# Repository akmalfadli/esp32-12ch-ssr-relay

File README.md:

# ESP32 + W5500 WebServer

## Overview
The Wemos32 12-Channel SSR Relay Controller is a smart switching system based on the ESP32 development board. It utilizes Solid State Relays (SSR) for controlling AC loads and features an Ethernet module (W5500) for network communication. The design is optimized for industrial and home automation applications, offering secure, remote-controlled relay switching.

## Features
Features

- ESP32-based control with Wi-Fi and Ethernet connectivity.
- 12-channel SSR relay control using G3MB-202P relays.
- W5500 Ethernet module for reliable wired communication.
- OLED 0.96-inch display for status monitoring.
- Secure API for remote control using authentication.
- Power supply management with AMS1117 3.3V regulator.
- Fuse protection for safety.

## Hardware Components
### 1. **Microcontroller**
- **ESP32-DEVKITC-32D** (provides Wi-Fi and Ethernet control)
- **Connected to W5500 Ethernet module** via SPI

### 2. **Relay Switching System**
- **12x G3MB-202P SSR relays** for AC load switching
- **Transistor drivers (SS8050)** for relay activation
- **LED indicators** for relay status

### 3. **Power Supply**
- **5V to 3.3V AMS1117 voltage regulator**
- **Multiple fuses for overcurrent protection**
- **External power input via barrel jack**

## Wiring Diagram
| Component | ESP32 Pin |
|-----------|----------|
| W5500 SPI MISO | GPIO 19 |
| W5500 SPI MOSI | GPIO 23 |
| W5500 SPI SCK  | GPIO 18 |
| W5500 SPI CS   | GPIO 5  |
| W5500 INT      | GPIO 4  |
| OLED SDA       | GPIO 21 |
| OLED SCL       | GPIO 22 |
| Relay 1-12     | GPIO 2, 16, 17, 13, 15, 14, 12, 25, 26, 33, 32, 27 |

## Installation & Setup
1. **Install Arduino IDE** (if not installed already).
2. **Install ESP32 Board Package**:
   - Open Arduino IDE.
   - Go to `File` > `Preferences`.
   - Add `https://dl.espressif.com/dl/package_esp32_index.json` to "Additional Board Manager URLs".
   - Go to `Tools` > `Board` > `Boards Manager`.
   - Search for `ESP32` and install the latest version.
3. **Install Required Libraries**
4. **Upload Code**:
   - Open the Arduino sketch.
   - Select your board (`ESP32 Wrover Module`).
   - Connect the ESP32 and upload the code.
   - Github repo for Arduino code [a link](https://github.com/akmalfadli/esp32-12ch-eth)

## Static IP Configuration
Modify the `setup()` function in your Arduino sketch:
```cpp
Ethernet.begin(mac, ip, myDns, gateway, subnet);
```
Example static IP settings:
```cpp
IPAddress ip(192, 168, 11, 51);
IPAddress gateway(192, 168, 11, 1);
IPAddress subnet(255, 255, 255, 0);
IPAddress myDns(8, 8, 8, 8);
```

## API Endpoints
| Method | Endpoint        | Description          |
|--------|----------------|----------------------|
| GET    | `/relay-state?ch=`      | Get device status   |
| POST   | `/relay?ch=2&state=0`    | Turn relay ON and OFF      |
| POST   | `set-auth?new-key`   |Set bearer token key     |

## Troubleshooting
### Compilation Errors
- **Ensure ESP32 is selected** in `Tools` > `Board`.
- **Check for duplicate libraries** in `Arduino/libraries/` and remove conflicting versions.
- **Reduce SPI clock speed** if Ethernet is unstable:
  ```cpp
  #define ETH_SPI_CLOCK 8000000  // Set to 8MHz
  ```

## Troubleshooting
- **No Ethernet Connection** → Check **W5500 wiring** and **IP settings**.
- **Relays not Switching** → Ensure **power supply** and **correct GPIO connections**.
- **OLED Display not Working** → Confirm **I2C address (default: 0x3C)**.

## Future Enhancements
- **Add MQTT for IoT integration**.
- **Web-based control panel** for easier relay management.
- **RTC for scheduled relay operations**.

## License
This project is open-source and licensed under the MIT License.

---
Made with ❤️ by Akmal Fadli - Perwira Teknologi Informasi

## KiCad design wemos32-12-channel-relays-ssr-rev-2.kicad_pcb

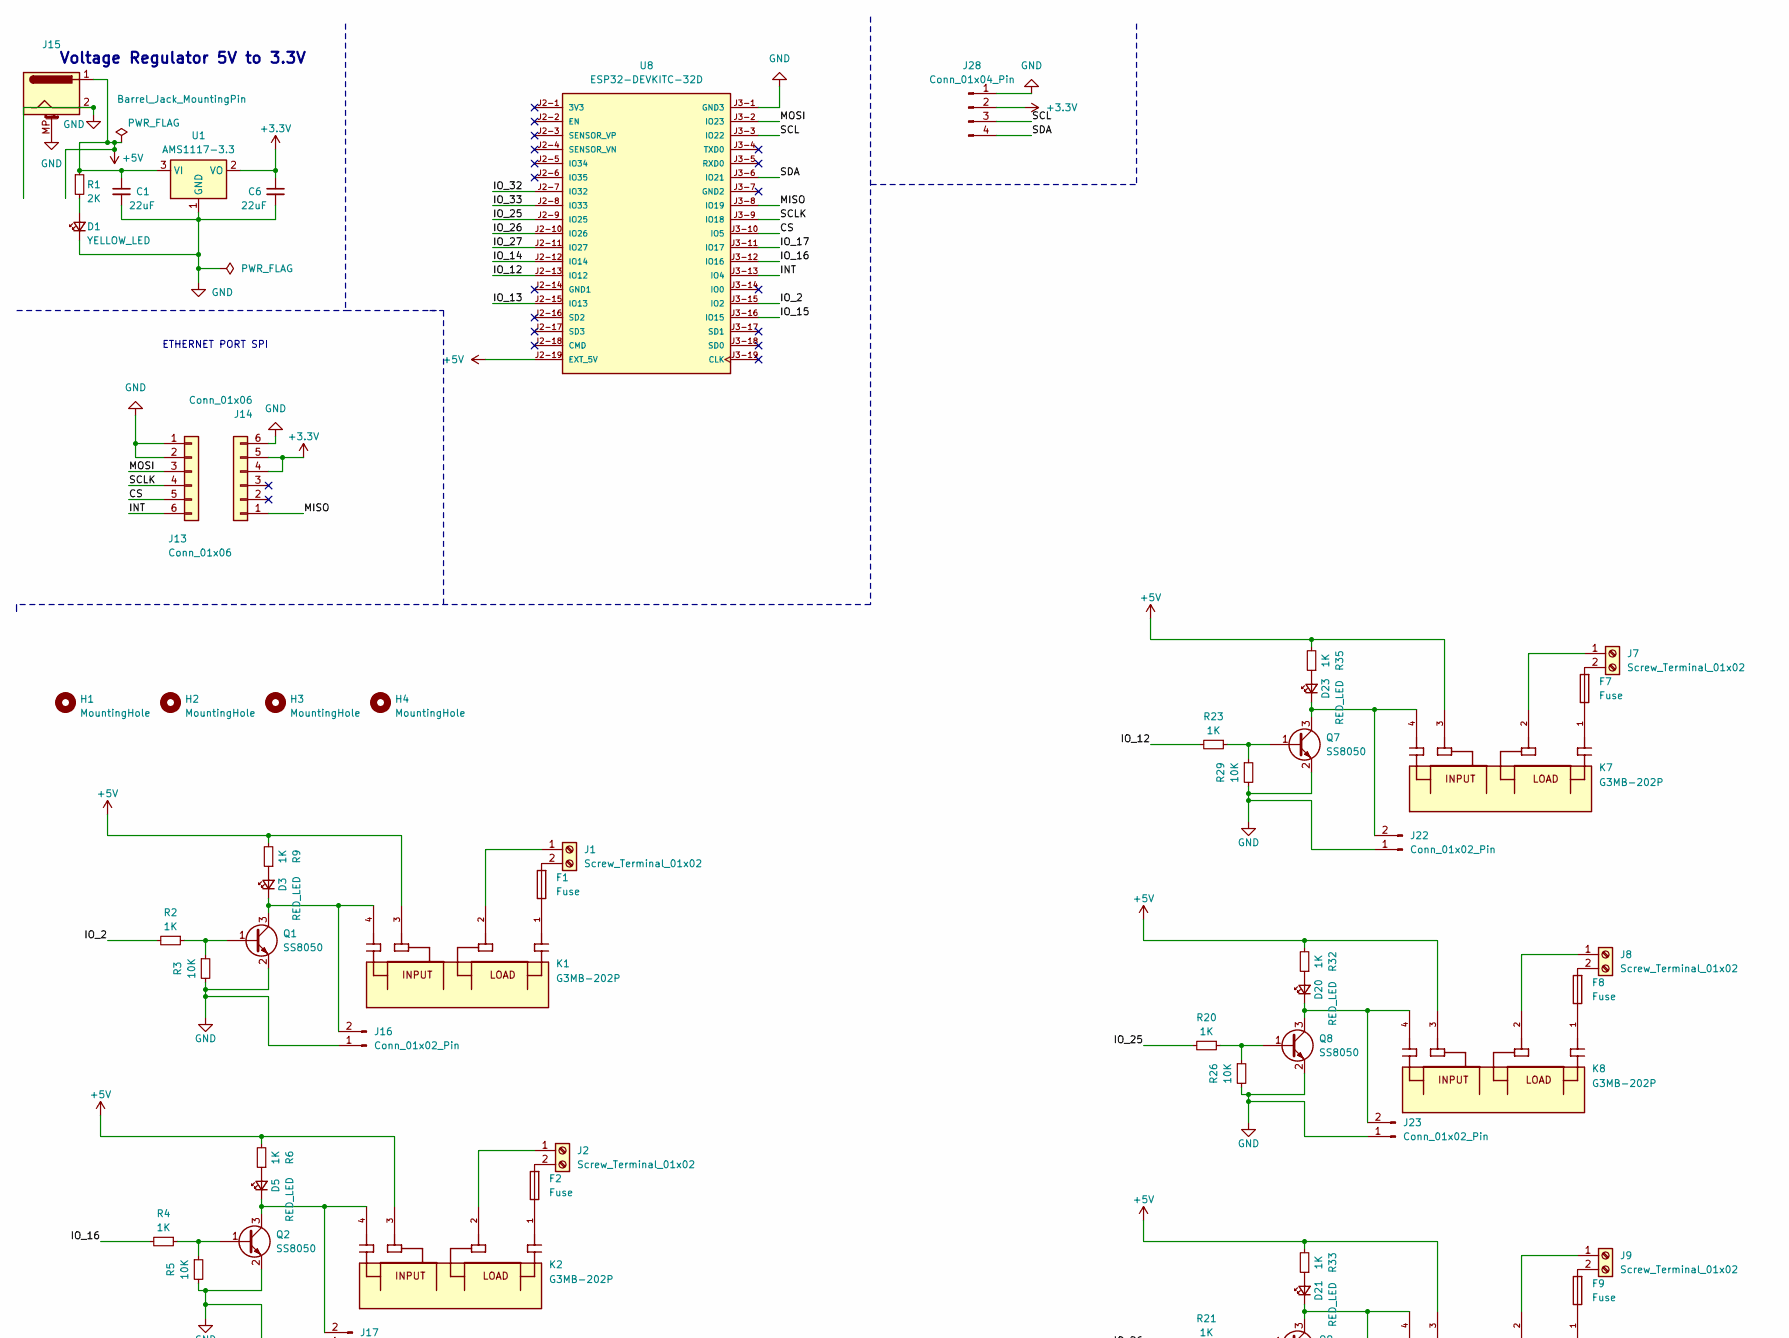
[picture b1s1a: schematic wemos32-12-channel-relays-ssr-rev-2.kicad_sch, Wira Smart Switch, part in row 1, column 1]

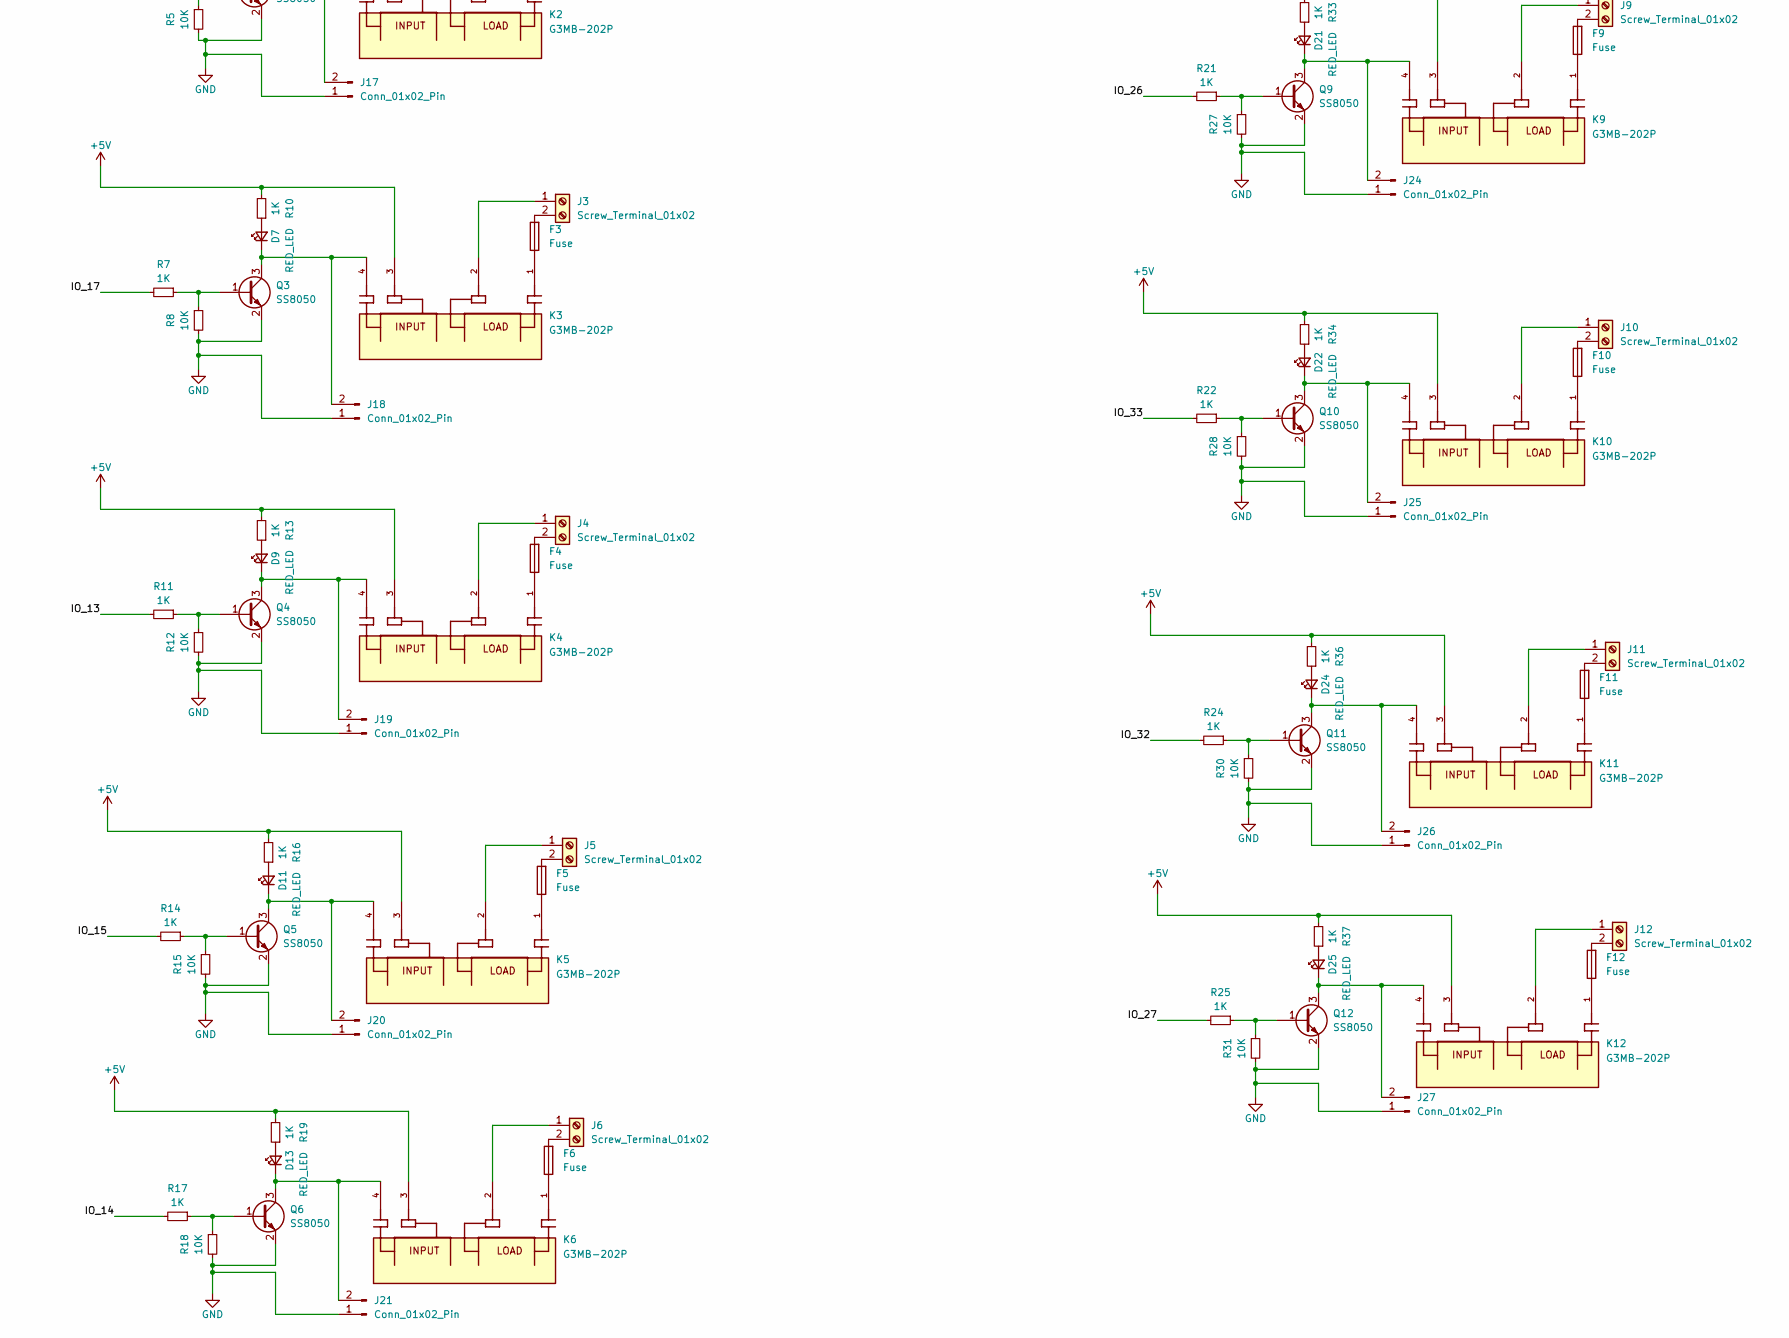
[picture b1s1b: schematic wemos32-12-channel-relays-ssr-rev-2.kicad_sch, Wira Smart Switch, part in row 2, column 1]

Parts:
C1, C6: 22uF; C_0805_2012Metric_Pad1.18x1.45mm_HandSolder
D1: YELLOW_LED; LED_0805_2012Metric_Pad1.15x1.40mm_HandSolder
D3, D5, D7, D9, D11, D13, D20, D21, D22, D23, D24, D25: RED_LED; LED_0805_2012Metric_Pad1.15x1.40mm_HandSolder
F1, F2, F3, F4, F5, F6, F7, F8, F9, F10, F11, F12: Fuse; Fuseholder_Littelfuse_100_series_5x20mm
H1, H2, H3, H4: MountingHole; MountingHole_3.2mm_M3_DIN965_Pad
J1, J2, J3, J4, J5, J6, J7, J8, J9, J10, J11, J12: Screw_Terminal_01x02; TerminalBlock_Wuerth_691311400102_P7.62mm
J13, J14: Conn_01x06; PinHeader_1x06_P2.54mm_Vertical
J15: Barrel_Jack_MountingPin; BarrelJack_Horizontal
J16, J17, J18, J19, J20, J21, J22, J23, J24, J25, J26, J27: Conn_01x02_Pin; JST_EH_B2B-EH-A_1x02_P2.50mm_Vertical
J28: Conn_01x04_Pin; PinHeader_1x04_P2.54mm_Vertical
K1, K2, K3, K4, K5, K6, K7, K8, K9, K10, K11, K12: G3MB-202P; RELAY_G3MB-202P; PARTREV J091-E1-1A
Q1, Q2, Q3, Q4, Q5, Q6, Q7, Q8, Q9, Q10, Q11, Q12: SS8050; SOT-23
R1: 2K; R_0805_2012Metric_Pad1.20x1.40mm_HandSolder
R2, R4, R6, R7, R9, R10, R11, R13, R14, R16, R17, R19, R20, R21, R22, R23, R24, R25, R32, R33, R34, R35, R36, R37: 1K; R_0805_2012Metric_Pad1.20x1.40mm_HandSolder
R3, R5, R8, R12, R15, R18, R26, R27, R28, R29, R30, R31: 10K; R_0805_2012Metric_Pad1.20x1.40mm_HandSolder
U1: AMS1117-3.3; SOT-223-3_TabPin2
U8: ESP32-DEVKITC-32D; MODULE_ESP32-DEVKITC-32D; PARTREV V4

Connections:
+3.3V: C6.1, J14.4, J14.5, J28.2, U1.2 (VO)
+5V: C1.1, J15.1, K1.3, K2.3, K3.3, K4.3, K5.3, K6.3, K7.3, K8.3, K9.3, K10.3, K11.3, K12.3, R1.1, R6.2, R9.2, R10.2, R13.2, R16.2, R19.2, R32.2, R33.2, R34.2, R35.2, R36.2, R37.2, U1.3 (VI), U8.J2-19 (EXT_5V)
/CS: J13.5, U8.J3-10 (IO5)
/INT: J13.6, U8.J3-13 (IO4)
/IO_2: R2.2, U8.J3-15 (IO2)
/IO_12: R23.2, U8.J2-13 (IO12)
/IO_13: R11.2, U8.J2-15 (IO13)
/IO_14: R17.2, U8.J2-12 (IO14)
/IO_15: R14.2, U8.J3-16 (IO15)
/IO_16: R4.2, U8.J3-12 (IO16)
/IO_17: R7.2, U8.J3-11 (IO17)
/IO_25: R20.2, U8.J2-9 (IO25)
/IO_26: R21.2, U8.J2-10 (IO26)
/IO_27: R25.2, U8.J2-11 (IO27)
/IO_32: R24.2, U8.J2-7 (IO32)
/IO_33: R22.2, U8.J2-8 (IO33)
/MISO: J14.1, U8.J3-8 (IO19)
/MOSI: J13.3, U8.J3-2 (IO23)
/SCL: J28.3, U8.J3-3 (IO22)
/SCLK: J13.4, U8.J3-9 (IO18)
/SDA: J28.4, U8.J3-6 (IO21)
GND: C1.2, C6.2, D1.1 (K), J13.1, J13.2, J14.6, J15.2, J15.MP (MountPin), J16.1, J17.1, J18.1, J19.1, J20.1, J21.1, J22.1, J23.1, J24.1, J25.1, J26.1, J27.1, J28.1, Q1.2 (E), Q2.2 (E), Q3.2 (E), Q4.2 (E), Q5.2 (E), Q6.2 (E), Q7.2 (E), Q8.2 (E), Q9.2 (E), Q10.2 (E), Q11.2 (E), Q12.2 (E), R3.2, R5.2, R8.2, R12.2, R15.2, R18.2, R26.2, R27.2, R28.2, R29.2, R30.2, R31.2, U1.1 (GND), U8.J3-1 (GND3)
unnamed: D1.2 (A), R1.2
unnamed: D3.2 (A), R9.1
unnamed: D3.1 (K), J16.2, K1.4, Q1.3 (C)
unnamed: D5.2 (A), R6.1
unnamed: D5.1 (K), J17.2, K2.4, Q2.3 (C)
unnamed: D7.2 (A), R10.1
unnamed: D7.1 (K), J18.2, K3.4, Q3.3 (C)
unnamed: D9.2 (A), R13.1
unnamed: D9.1 (K), J19.2, K4.4, Q4.3 (C)
unnamed: D11.2 (A), R16.1
unnamed: D11.1 (K), J20.2, K5.4, Q5.3 (C)
unnamed: D13.2 (A), R19.1
unnamed: D13.1 (K), J21.2, K6.4, Q6.3 (C)
unnamed: D20.2 (A), R32.1
unnamed: D20.1 (K), J23.2, K8.4, Q8.3 (C)
unnamed: D21.2 (A), R33.1
unnamed: D21.1 (K), J24.2, K9.4, Q9.3 (C)
unnamed: D22.2 (A), R34.1
unnamed: D22.1 (K), J25.2, K10.4, Q10.3 (C)
unnamed: D23.2 (A), R35.1
unnamed: D23.1 (K), J22.2, K7.4, Q7.3 (C)
unnamed: D24.2 (A), R36.1
unnamed: D24.1 (K), J26.2, K11.4, Q11.3 (C)
unnamed: D25.2 (A), R37.1
unnamed: D25.1 (K), J27.2, K12.4, Q12.3 (C)
unnamed: F1.1, K1.1
unnamed: F2.1, K2.1
unnamed: F3.1, K3.1
unnamed: F4.1, K4.1
unnamed: F5.1, K5.1
unnamed: F6.1, K6.1
unnamed: F7.1, K7.1
unnamed: F8.1, K8.1
unnamed: F9.1, K9.1
unnamed: F10.1, K10.1
unnamed: F11.1, K11.1
unnamed: F12.1, K12.1
unnamed: J1.1, K1.2
unnamed: F1.2, J1.2
unnamed: J2.1, K2.2
unnamed: F2.2, J2.2
unnamed: J3.1, K3.2
unnamed: F3.2, J3.2
unnamed: J4.1, K4.2
unnamed: F4.2, J4.2
unnamed: J5.1, K5.2
unnamed: F5.2, J5.2
unnamed: J6.1, K6.2
unnamed: F6.2, J6.2
unnamed: J7.1, K7.2
unnamed: F7.2, J7.2
unnamed: J8.1, K8.2
unnamed: F8.2, J8.2
unnamed: J9.1, K9.2
unnamed: F9.2, J9.2
unnamed: J10.1, K10.2
unnamed: F10.2, J10.2
unnamed: J11.1, K11.2
unnamed: F11.2, J11.2
unnamed: J12.1, K12.2
unnamed: F12.2, J12.2
unnamed: Q1.1 (B), R2.1, R3.1
unnamed: Q2.1 (B), R4.1, R5.1
unnamed: Q3.1 (B), R7.1, R8.1
unnamed: Q4.1 (B), R11.1, R12.1
unnamed: Q5.1 (B), R14.1, R15.1
unnamed: Q6.1 (B), R17.1, R18.1
unnamed: Q7.1 (B), R23.1, R29.1
unnamed: Q8.1 (B), R20.1, R26.1
unnamed: Q9.1 (B), R21.1, R27.1
unnamed: Q10.1 (B), R22.1, R28.1
unnamed: Q11.1 (B), R24.1, R30.1
unnamed: Q12.1 (B), R25.1, R31.1

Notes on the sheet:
Voltage Regulator 5V to 3.3V
ETHERNET PORT SPI

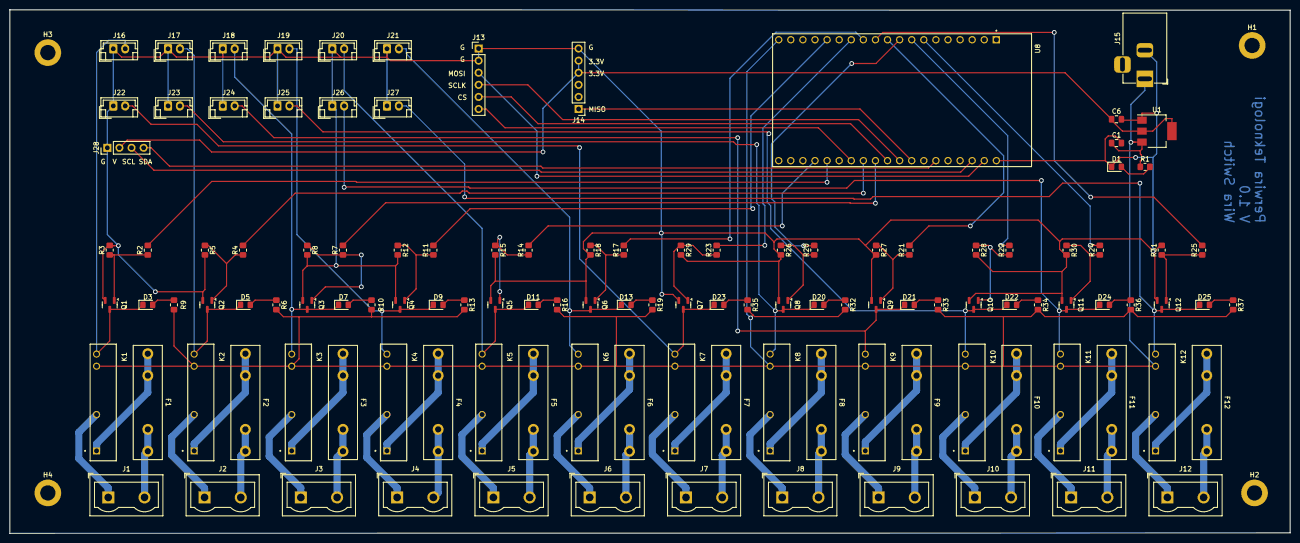
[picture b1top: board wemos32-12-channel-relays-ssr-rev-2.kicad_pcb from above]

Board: 2 copper layers, 269.0 x 110.0 mm, 122 parts (0 on the bottom side), 95 nets.

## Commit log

2025-03-22 first upload
2025-03-22 taking 3d design
2025-03-22 add readme file
2025-03-22 fix readme file
2025-03-22 add schematic
